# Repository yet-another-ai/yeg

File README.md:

# yeg
Yet Another Open-source EEG Device

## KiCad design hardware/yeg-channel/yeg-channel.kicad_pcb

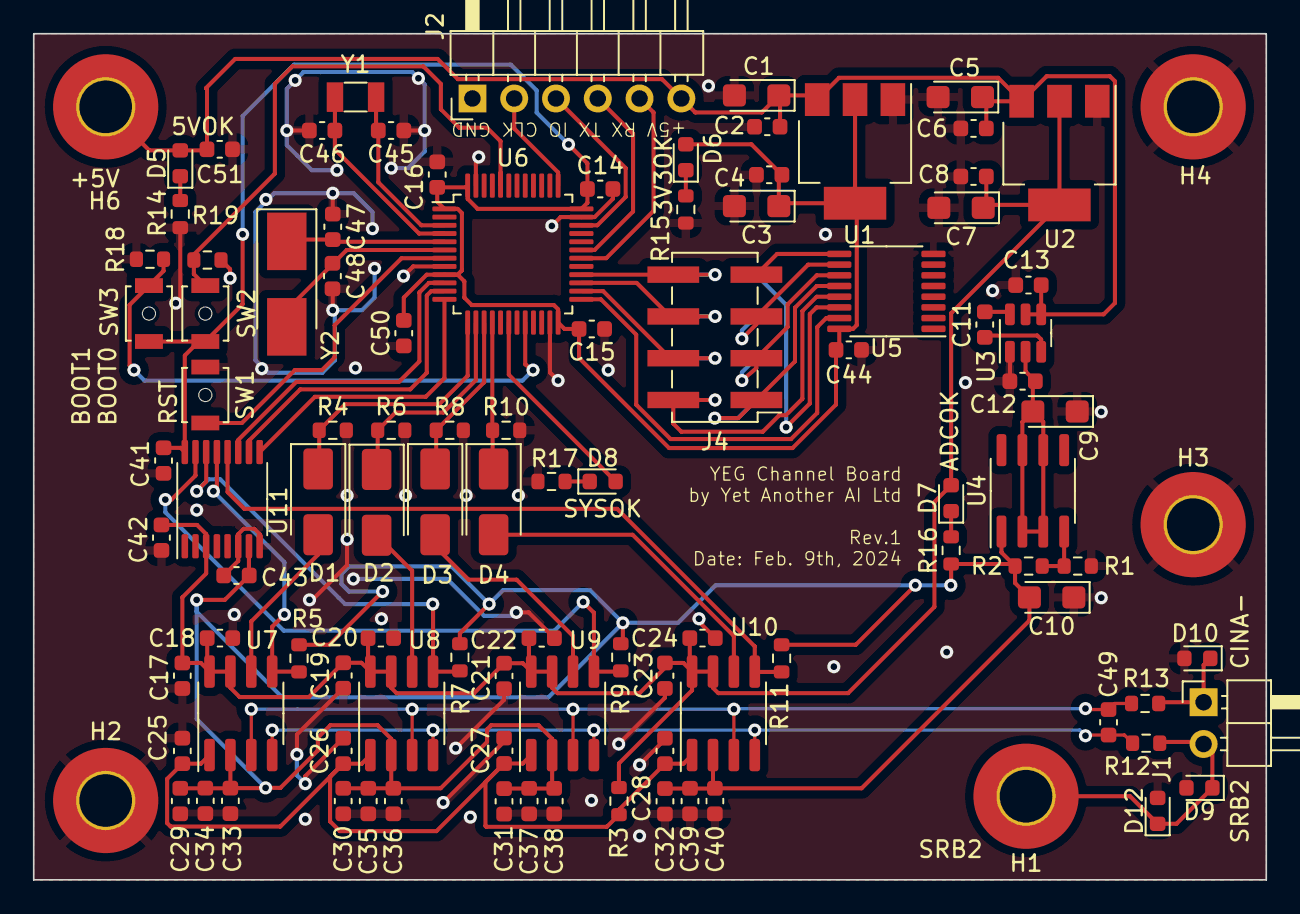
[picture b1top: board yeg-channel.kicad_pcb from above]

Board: 2 copper layers, 74.9 x 51.4 mm, 106 parts (1 on the bottom side), 55 nets.

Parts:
C1, C3, C5, C7: 22u; CP_EIA-3216-10_Kemet-I
C2, C4, C6, C8, C13, C14, C15, C16, C17, C18, C19, C20, C21, C22, C23, C24, C25, C26, C27, C28, C29, C30, C31, C32, C33, C34, C35, C36, C37, C38, C39, C40, C41, C42, C43, C44, C49, C50, C51: 100n; C_0603_1608Metric
C9, C10: 1u; CP_EIA-3216-10_Kemet-I
C11, C12: 3.3u; C_0603_1608Metric
C45, C46: 12p; C_0603_1608Metric
C47, C48: 20p; C_0603_1608Metric
D1, D2, D3, D4: SS14; D_SMA
D5: LED_5VOK; LED_0603_1608Metric
D6: LED_3V3OK; LED_0603_1608Metric
D7: LED_ADCOK; LED_0603_1608Metric
D8: LED_SYSOK; LED_0603_1608Metric
D9, D10, D12: D_TVS; D_0603_1608Metric
H1: SRB2; MountingHole_3.2mm_M3_Pad_TopBottom
H2, H3, H4: GND; MountingHole_3.2mm_M3_Pad_TopBottom
H6: 5V; MountingHole_3.2mm_M3_Pad_TopBottom
J1: Conn_ADC; PinHeader_1x02_P2.54mm_Horizontal
J2: Conn_Debug; PinHeader_1x06_P2.54mm_Horizontal
J3: Conn_SPI_Input; PinSocket_2x04_P2.54mm_Vertical_SMD
J4: Conn_SPI_Output; PinHeader_2x04_P2.54mm_Vertical_SMD
R1, R2: 240; R_0603_1608Metric
R3: 10; R_0603_1608Metric
R4, R6, R8, R10: 40k; R_0603_1608Metric
R5, R7, R9, R11, R18, R19: 10k; R_0603_1608Metric
R12, R13: 200; R_0603_1608Metric
R14, R16: 100; R_0603_1608Metric
R15, R17: 24; R_0603_1608Metric
SW1: SW_RST; SW_SPST_B3U-1000P-B
SW2: SW_BOOT0; SW_SPST_B3U-1000P-B
SW3: SW_BOOT1; SW_SPST_B3U-1000P-B
U1: AMS1117-3.3; SOT-223-3_TabPin2
U2: AMS1117-2.5; SOT-223-3_TabPin2
U3: LM2664M6X; SOT-23-6
U4: LM337L_SO8; SOIC-8_3.9x4.9mm_P1.27mm
U5: 74HC595; TSSOP-16_4.4x5mm_P0.65mm
U6: CH32V103C8T6; LQFP-48_7x7mm_P0.5mm
U7, U8, U9, U10: HX71708; SOP-8_3.76x4.96mm_P1.27mm
U11: 74HC4051; TSSOP-16_4.4x5mm_P0.65mm
Y1: 32.768k; Crystal_SMD_3215-2Pin_3.2x1.5mm
Y2: 8M; Crystal_SMD_5032-2Pin_5.0x3.2mm_HandSoldering

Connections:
+2V5: C7.1, C8.1, C17.1, C18.1, C19.1, C20.1, C21.1, C22.1, C23.1, C24.1, C42.1, D7.2 (A), R3.1, U2.2 (VO), U7.7 (DVDD), U7.8 (AVDD), U8.7 (DVDD), U8.8 (AVDD), U9.7 (DVDD), U9.8 (AVDD), U10.7 (DVDD), U10.8 (AVDD), U11.3 (A)
+3V3: C3.1, C4.1, C14.1, C15.1, C16.1, C41.1, C44.1, C50.1, D6.2 (A), SW2.2, SW3.2, U1.2 (VO), U5.16 (VCC), U6.1 (VBAT), U6.9 (VDDA), U6.24 (VDD), U6.36 (VDD), U6.48 (VDD), U11.16 (VCC)
+5V: C1.1, C2.1, C5.1, C6.1, C13.1, C51.1, D5.2 (A), H6.1, J2.6, U1.3 (VI), U2.3 (VI), U3.4 (SD), U3.5 (V+)
-2V5: C10.2, C29.2, C30.2, C31.2, C32.2, C33.2, C34.2, C35.2, C36.2, C37.2, C38.2, C39.2, C40.2, C43.2, R2.2, R5.2, R7.2, R9.2, R11.2, R16.2, U4.1 (VO), U7.2 (GND), U8.2 (GND), U9.2 (GND), U10.2 (GND), U11.7 (VEE)
-5V: C9.2, C12.1, U3.2 (OUT), U4.2 (VI), U4.3 (VI), U4.6 (VI), U4.7 (VI)
/ADC/CINA-: D10.1 (A1), J1.1, R13.1
/ADC/CS0: U6.10 (PA0), U11.11 (S0)
/ADC/CS1: U6.11 (PA1), U11.10 (S1)
/ADC/CS2: U6.12 (PA2), U11.9 (S2)
/ADC/DOUT0: D1.1 (K), R4.1, U6.13 (PA3)
/ADC/DOUT1: D2.1 (K), R6.1, U6.14 (PA4)
/ADC/DOUT2: D3.1 (K), R8.1, U6.15 (PA5)
/ADC/DOUT3: D4.1 (K), R10.1, U6.16 (PA6)
/ADC/IN+: C49.1, R12.2, U7.4 (IN+), U8.4 (IN+), U9.4 (IN+), U10.4 (IN+)
/ADC/IN-: C49.2, R13.2, U7.3 (IN-), U8.3 (IN-), U9.3 (IN-), U10.3 (IN-)
/ADC/PD_SCK0: R5.1, U7.5 (PD_SCK), U11.13 (A0)
/ADC/PD_SCK1: R7.1, U8.5 (PD_SCK), U11.14 (A1)
/ADC/PD_SCK2: R9.1, U9.5 (PD_SCK), U11.15 (A2)
/ADC/PD_SCK3: R11.1, U10.5 (PD_SCK), U11.12 (A3)
/ADC/SRB2: D9.1 (A1), D12.1 (A1), H1.1, J1.2, R12.1
/Connector/BOOT0: R19.1, SW2.1, U6.44 (BOOT0)
/Connector/BOOT1: R18.1, SW3.1, U6.20 (PB2)
/Connector/CS_IN: J3.7, U5.14 (SER)
/Connector/CS_OUT: J4.7, U5.9 (QH')
/Connector/NRST: SW1.1, U6.7 (NRST)
/Connector/RCLK: J3.1, J4.1, U5.12 (RCLK)
/Connector/SPI_MISO: J3.6, J4.6, U6.27 (PB14)
/Connector/SPI_MOSI: J3.8, J4.8, U6.28 (PB15)
/Connector/SPI_SCK: J3.4, J4.4, U6.26 (PB13)
/Connector/SRCLK: J3.3, J4.3, U5.11 (SRCLK)
/Connector/SWDCLK: J2.2, U6.37 (PA14)
/Connector/SWDIO: J2.3, U6.34 (PA13)
/Connector/SYSOK: D8.2 (A), U6.18 (PB0)
/Connector/UART1_RX: J2.4, U6.31 (PA10)
/Connector/UART1_TX: J2.5, U6.30 (PA9)
/Connector/~OE: J3.2, J4.2, U5.13 (~OE)
/Connector/~SRCLR: J3.5, J4.5, U5.10 (~SRCLR)
/MCU/OSC32_IN: C45.2, U6.3 (PC14), Y1.1
/MCU/OSC32_OUT: C46.1, U6.4 (PC15), Y1.2
/MCU/OSC_IN: C47.2, U6.5 (PD0), Y2.1
/MCU/OSC_OUT: C48.1, U6.6 (PD1), Y2.2
/MCU/SPI_CS: U5.15 (QA), U6.25 (PB12)
GND: C1.2, C2.2, C3.2, C4.2, C5.2, C6.2, C7.2, C8.2, C9.1, C10.1, C12.2, C13.2, C14.2, C15.2, C16.2, C17.2, C18.2, C19.2, C20.2, C21.2, C22.2, C23.2, C24.2, C25.2, C26.2, C27.2, C28.2, C29.1, C30.1, C31.1, C32.1, C33.1, C34.1, C35.1, C36.1, C37.1, C38.1, C39.1, C40.1, C41.2, C42.2, C43.1, C44.2, C45.1, C46.2, C47.1, C48.2, C50.2, C51.2, D9.2 (A2), D10.2 (A2), D12.2 (A2), H2.1, H3.1, H4.1, J2.1, R1.1, R4.2, R6.2, R8.2, R10.2, R14.2, R15.2, R17.2, R18.2, R19.2, SW1.2, U1.1 (GND), U2.1 (GND), U3.1 (GND), U5.8 (GND), U6.8 (VSSA), U6.23 (VSS), U6.35 (VSS), U6.47 (VSS), U11.6 (~E), U11.8 (GND)
unnamed: D1.2 (A), U7.6 (DOUT)
unnamed: D2.2 (A), U8.6 (DOUT)
unnamed: D3.2 (A), U9.6 (DOUT)
unnamed: D4.2 (A), U10.6 (DOUT)
unnamed: D5.1 (K), R14.1
unnamed: D6.1 (K), R15.1
unnamed: D7.1 (K), R16.1
unnamed: D8.1 (K), R17.1
unnamed: C11.1, U3.6 (CAP+)
unnamed: C11.2, U3.3 (CAP-)
unnamed: R1.2, R2.1, U4.4 (ADJ)
VDDA: C25.1, C26.1, C27.1, C28.1, R3.2, U7.1 (VREF), U8.1 (VREF), U9.1 (VREF), U10.1 (VREF)

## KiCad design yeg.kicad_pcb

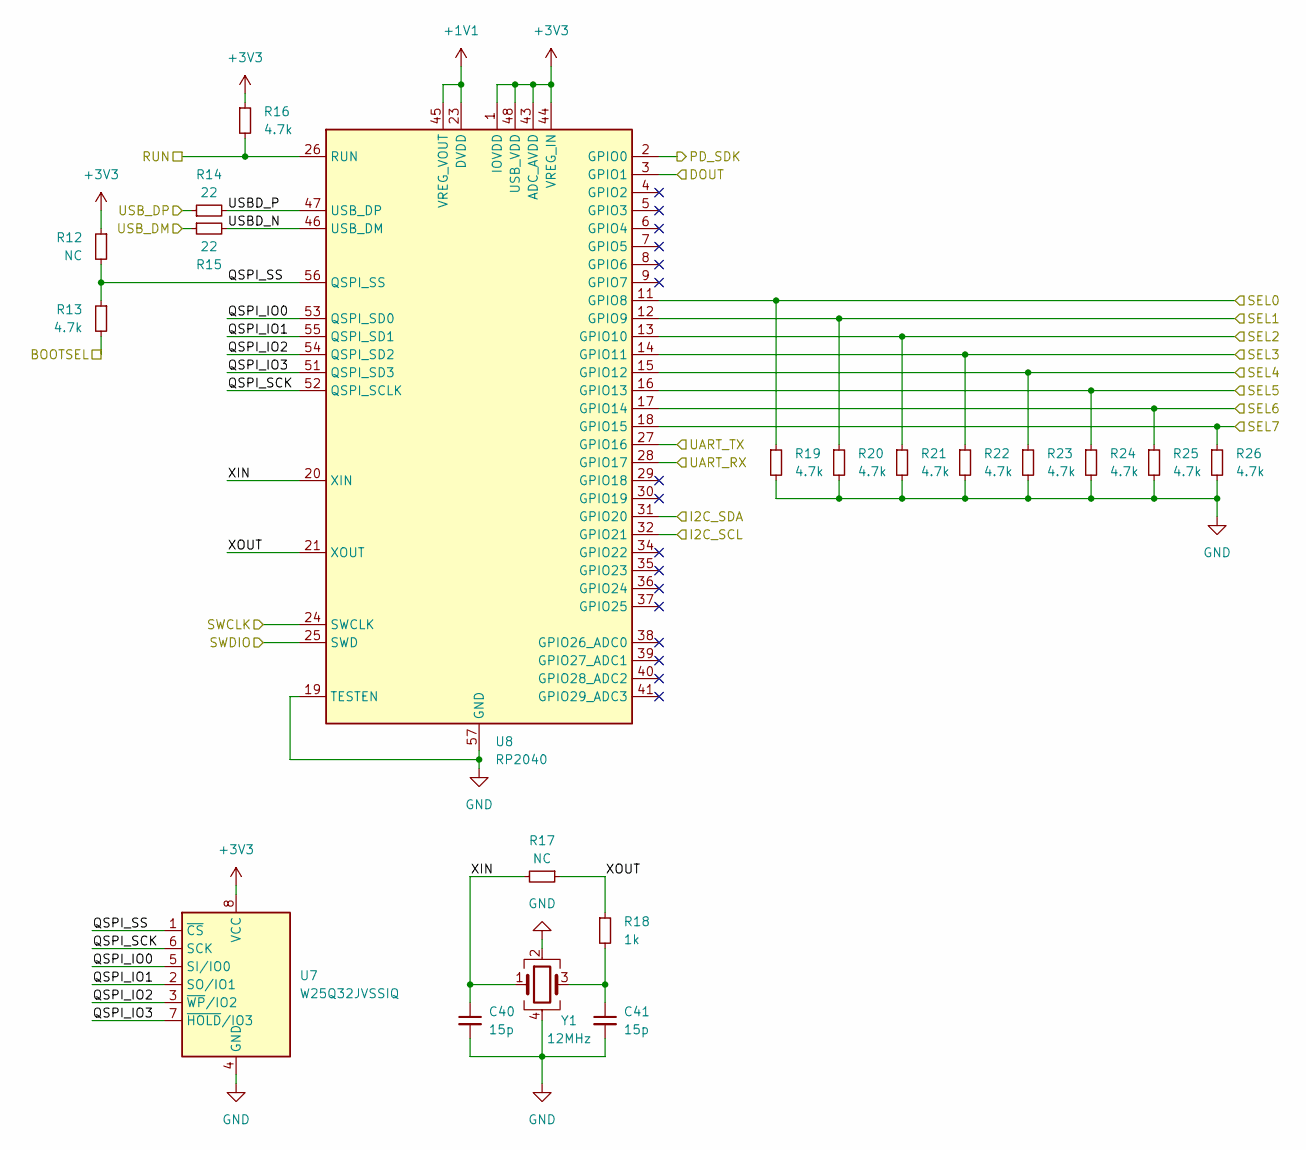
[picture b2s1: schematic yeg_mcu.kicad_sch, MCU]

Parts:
C40, C41: 15p; C_0603_1608Metric; LCSC Number C107037
R12, R17: NC; R_0603_1608Metric
R13, R16, R19, R20, R21, R22, R23, R24, R25, R26: 4.7k; R_0603_1608Metric; LCSC Number C23162
R14, R15: 22; R_0603_1608Metric; LCSC Number C23345
R18: 1k; R_0603_1608Metric; LCSC Number C21190
U7: W25Q32JVSSIQ; SOIC-8_5.275x5.275mm_P1.27mm; LCSC Number C179173
U8: RP2040; QFN-56-1EP_7x7mm_P0.4mm_EP3.2x3.2mm; LCSC Number C2040
Y1: 12MHz; Crystal_SMD_3225-4Pin_3.2x2.5mm; LCSC Number C9002

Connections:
+1V1: U8.23 (DVDD), U8.45 (VREG_VOUT), U8.50 (DVDD); also elsewhere on the board
+3V3: R12.1, R16.1, U7.8 (VCC), U8.1 (IOVDD), U8.10 (IOVDD), U8.22 (IOVDD), U8.33 (IOVDD), U8.42 (IOVDD), U8.43 (ADC_AVDD), U8.44 (VREG_IN), U8.48 (USB_VDD), U8.49 (IOVDD); also elsewhere on the board
/ADC/DOUT: U8.3 (GPIO1); also elsewhere on the board
/ADC/PD_SCK: U8.2 (GPIO0); also elsewhere on the board
/Connectors/BOOTSEL: R13.2; also elsewhere on the board
/Connectors/I2C_SCL: U8.32 (GPIO21); also elsewhere on the board
/Connectors/I2C_SDA: U8.31 (GPIO20); also elsewhere on the board
/Connectors/RUN: R16.2, U8.26 (RUN); also elsewhere on the board
/Connectors/SEL0: R19.1, U8.11 (GPIO8); also elsewhere on the board
/Connectors/SEL1: R20.1, U8.12 (GPIO9); also elsewhere on the board
/Connectors/SEL2: R21.1, U8.13 (GPIO10); also elsewhere on the board
/Connectors/SEL3: R22.1, U8.14 (GPIO11); also elsewhere on the board
/Connectors/SEL4: R23.1, U8.15 (GPIO12); also elsewhere on the board
/Connectors/SEL5: R24.1, U8.16 (GPIO13); also elsewhere on the board
/Connectors/SEL6: R25.1, U8.17 (GPIO14); also elsewhere on the board
/Connectors/SEL7: R26.1, U8.18 (GPIO15); also elsewhere on the board
/Connectors/SWCLK: U8.24 (SWCLK); also elsewhere on the board
/Connectors/SWDIO: U8.25 (SWD); also elsewhere on the board
/Connectors/UART_RX: U8.28 (GPIO17); also elsewhere on the board
/Connectors/UART_TX: U8.27 (GPIO16); also elsewhere on the board
/Connectors/USBDM: R15.1; also elsewhere on the board
/Connectors/USBDP: R14.1; also elsewhere on the board
/MCU/QSPI_IO0: U7.5 (SI/IO0), U8.53 (QSPI_SD0)
/MCU/QSPI_IO1: U7.2 (SO/IO1), U8.55 (QSPI_SD1)
/MCU/QSPI_IO2: U7.3 (~WP/IO2), U8.54 (QSPI_SD2)
/MCU/QSPI_IO3: U7.7 (~HOLD/IO3), U8.51 (QSPI_SD3)
/MCU/QSPI_SCK: U7.6 (SCK), U8.52 (QSPI_SCLK)
/MCU/QSPI_SS: R12.2, R13.1, U7.1 (~CS), U8.56 (QSPI_SS)
/MCU/USBD_N: R15.2, U8.46 (USB_DM)
/MCU/USBD_P: R14.2, U8.47 (USB_DP)
/MCU/XIN: C40.1, R17.2, U8.20 (XIN), Y1.1
/MCU/XOUT: R17.1, R18.1, U8.21 (XOUT)
GND: C40.2, C41.2, R19.2, R20.2, R21.2, R22.2, R23.2, R24.2, R25.2, R26.2, U7.4 (GND), U8.19 (TESTEN), U8.57 (GND), Y1.2, Y1.4; also elsewhere on the board
unnamed: C41.1, R18.2, Y1.3

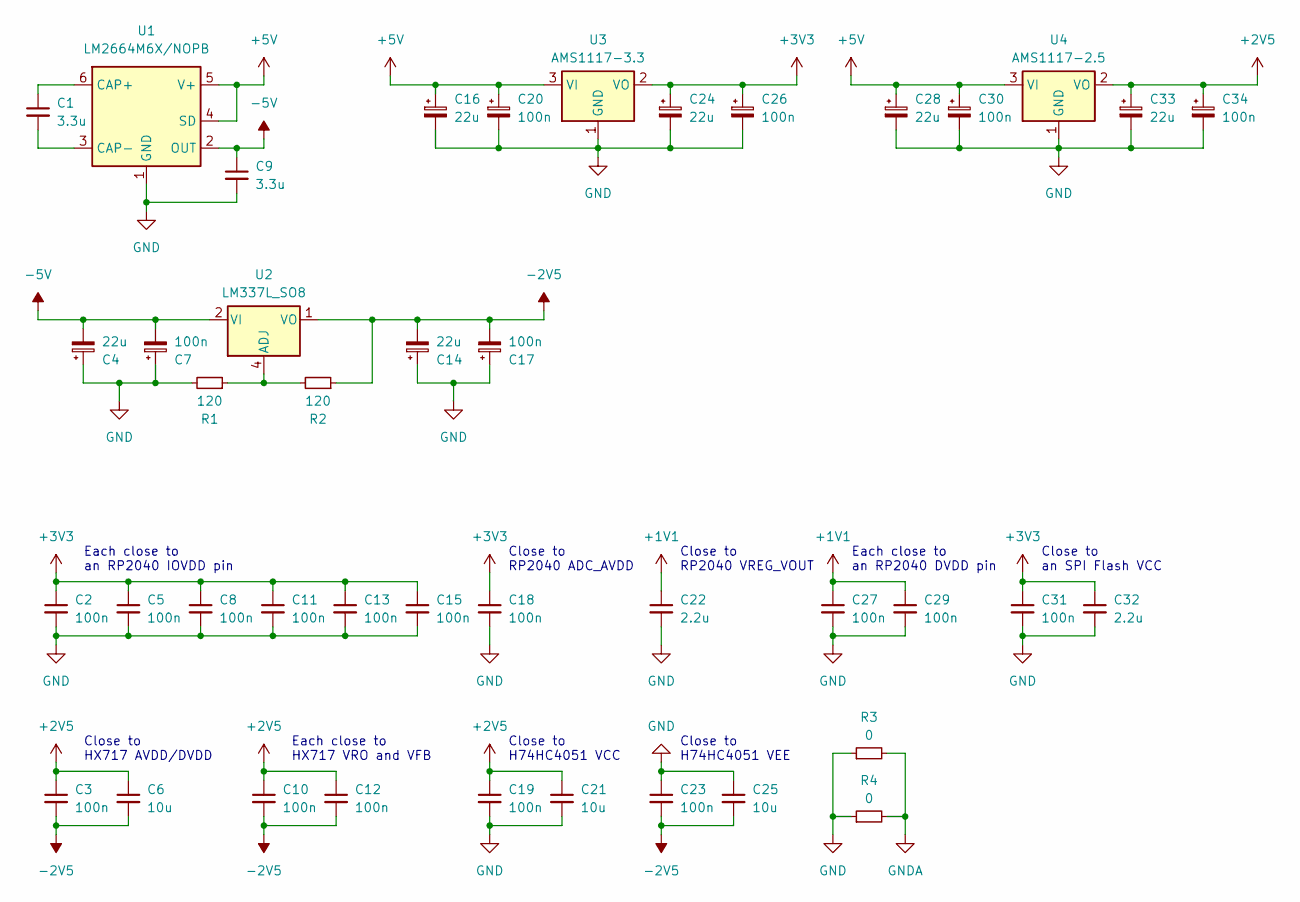
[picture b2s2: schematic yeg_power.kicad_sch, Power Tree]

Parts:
C1, C9: 3.3u; C_0603_1608Metric; LCSC Number C51412
C2, C3, C5, C8, C10, C11, C12, C13, C15, C18, C19, C23, C27, C29, C31: 100n; C_0603_1608Metric; LCSC Number C14663
C4, C14, C16, C24, C28, C33: 22u; C_1206_3216Metric; LCSC Number C1953590
C6, C21, C25: 10u; C_0603_1608Metric; LCSC Number C19702
C7, C17, C20, C26, C30, C34: 100n; C_1206_3216Metric; LCSC Number C1952859
C22, C32: 2.2u; C_0603_1608Metric; LCSC Number C23630
R1, R2: 120; R_0603_1608Metric; LCSC Number C22787
R3, R4: 0; R_0603_1608Metric; LCSC Number C21189
U1: LM2664M6X/NOPB; SOT-23-6; LCSC Number C108573
U2: LM337L_SO8; SOIC-8_3.9x4.9mm_P1.27mm; LCSC Number C544819
U3: AMS1117-3.3; SOT-223-3_TabPin2; LCSC Number C347222
U4: AMS1117-2.5; SOT-223-3_TabPin2; LCSC Number C347221

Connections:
+1V1: C22.1, C27.1, C29.1; also elsewhere on the board
+2V5: C3.1, C6.1, C10.1, C12.1, C19.1, C21.1, C33.1, C34.1, U4.2 (VO); also elsewhere on the board
+3V3: C2.1, C5.1, C8.1, C11.1, C13.1, C15.1, C18.1, C24.1, C26.1, C31.1, C32.1, U3.2 (VO); also elsewhere on the board
+5V: C16.1, C20.1, C28.1, C30.1, U1.4 (SD), U1.5 (V+), U3.3 (VI), U4.3 (VI); also elsewhere on the board
-2V5: C3.2, C6.2, C10.2, C12.2, C14.2, C17.2, C23.2, C25.2, R2.1, U2.1 (VO); also elsewhere on the board
-5V: C4.2, C7.2, C9.1, U1.2 (OUT), U2.2 (VI), U2.3 (VI), U2.6 (VI), U2.7 (VI)
GND: C2.2, C4.1, C5.2, C7.1, C8.2, C9.2, C11.2, C13.2, C14.1, C15.2, C16.2, C17.1, C18.2, C19.2, C20.2, C21.2, C22.2, C23.1, C24.2, C25.1, C26.2, C27.2, C28.2, C29.2, C30.2, C31.2, C32.2, C33.2, C34.2, R1.2, R3.1, R4.1, U1.1 (GND), U3.1 (GND), U4.1 (GND); also elsewhere on the board
GNDA: R3.2, R4.2; also elsewhere on the board
unnamed: C1.1, U1.6 (CAP+)
unnamed: C1.2, U1.3 (CAP-)
unnamed: R1.1, R2.2, U2.4 (ADJ)

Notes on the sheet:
Close to H74HC4051 VEE
Close to RP2040 VREG_VOUT
Each close to an RP2040 IOVDD pin
Close to RP2040 ADC_AVDD
Each close to HX717 VRO and VFB
Each close to an RP2040 DVDD pin
Close to an SPI Flash VCC
Close to HX717 AVDD/DVDD
Close to H74HC4051 VCC

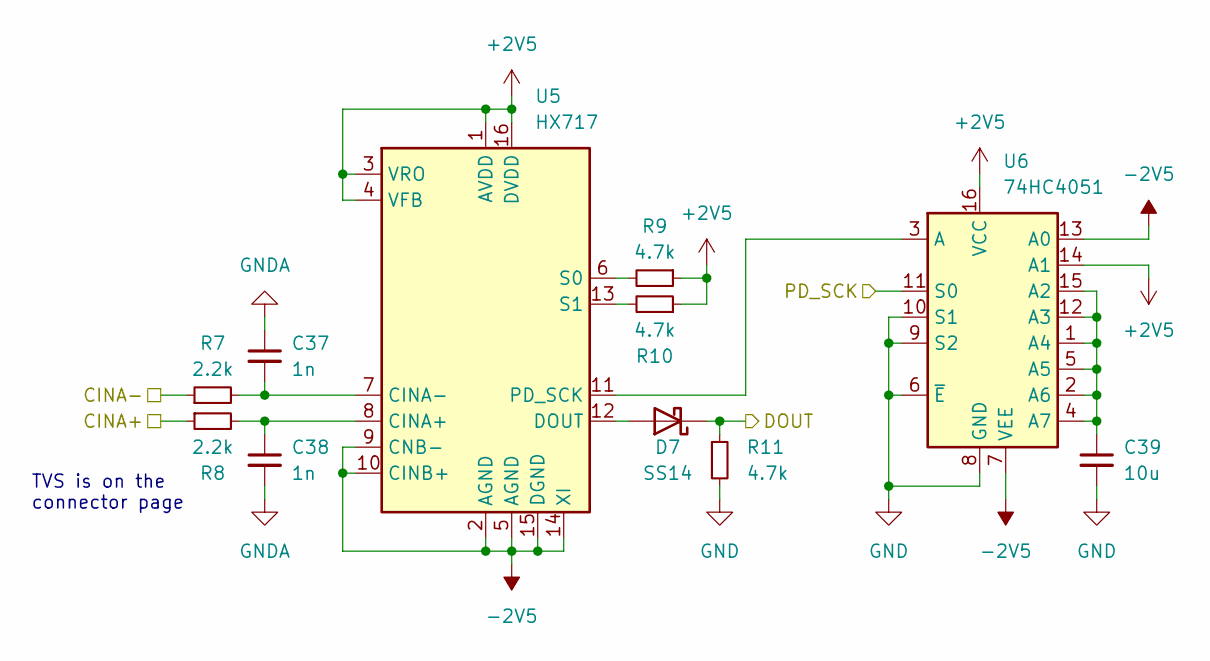
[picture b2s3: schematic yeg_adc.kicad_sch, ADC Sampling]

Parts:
C37, C38: 1n; C_0603_1608Metric; LCSC Number C100040
C39: 10u; C_0603_1608Metric; LCSC Number C19702
D7: SS14; D_SMA; LCSC Number C83852
R7, R8: 2.2k; R_0603_1608Metric; LCSC Number C4190
R9, R10, R11: 4.7k; R_0603_1608Metric; LCSC Number C23162
U5: HX717; SOP-16_4.55x10.3mm_P1.27mm; LCSC Number C2961106
U6: 74HC4051; SOP-16_3.9x9.9mm_P1.27mm; LCSC Number C507180

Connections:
+2V5: R9.1, R10.1, U5.1 (AVDD), U5.3 (VRO), U5.4 (VFB), U5.16 (DVDD), U6.14 (A1), U6.16 (VCC); also elsewhere on the board
-2V5: U5.2 (AGND), U5.5 (AGND), U5.9 (CNB-), U5.10 (CINB+), U5.14 (XI), U5.15 (DGND), U6.7 (VEE), U6.13 (A0); also elsewhere on the board
/ADC/CINA+: R8.1; also elsewhere on the board
/ADC/CINA-: R7.1; also elsewhere on the board
/ADC/DOUT: D7.1 (K), R11.1; also elsewhere on the board
/ADC/PD_SCK: U6.11 (S0); also elsewhere on the board
GND: C39.2, R11.2, U6.6 (~E), U6.8 (GND), U6.9 (S2), U6.10 (S1); also elsewhere on the board
GNDA: C37.1, C38.2; also elsewhere on the board
unnamed: D7.2 (A), U5.12 (DOUT)
unnamed: C38.1, R8.2, U5.8 (CINA+)
unnamed: C37.2, R7.2, U5.7 (CINA-)
unnamed: U5.11 (PD_SCK), U6.3 (A)
unnamed: R9.2, U5.6 (S0)
unnamed: R10.2, U5.13 (S1)
unnamed: C39.1, U6.1 (A4), U6.2 (A6), U6.4 (A7), U6.5 (A5), U6.12 (A3), U6.15 (A2)

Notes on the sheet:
TVS is on the connector page

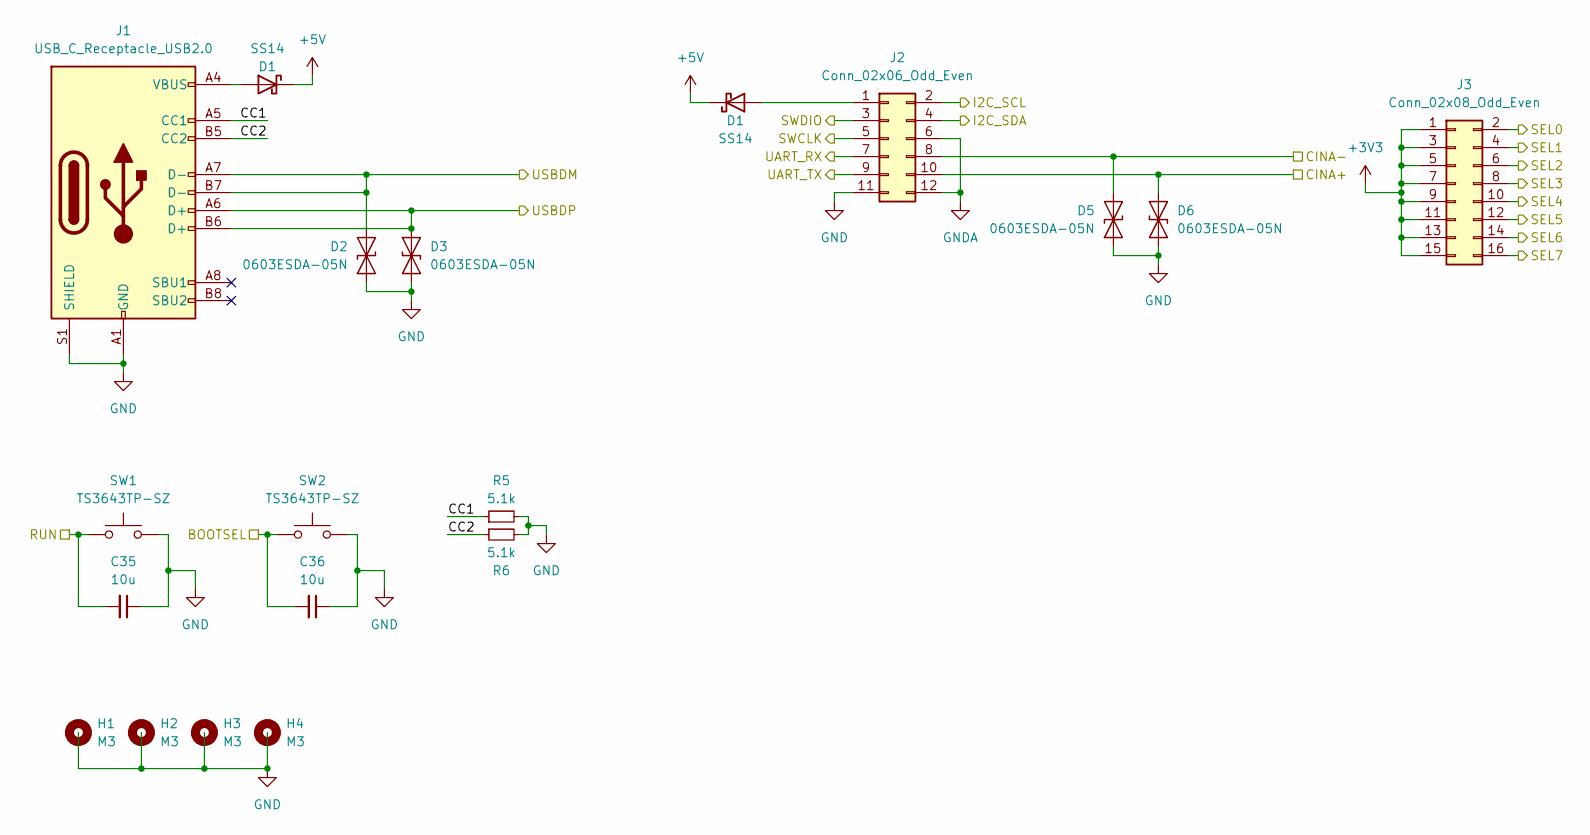
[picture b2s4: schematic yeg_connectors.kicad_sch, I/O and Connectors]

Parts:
C35, C36: 10u; C_0603_1608Metric; LCSC Number C19702
D1: SS14; D_SMA; LCSC Number C83852
D2, D3, D5, D6: 0603ESDA-05N; D_0603_1608Metric; LCSC Number C316054
H1, H2, H3, H4: M3; MountingHole_3.2mm_M3_DIN965_Pad
J1: USB_C_Receptacle_USB2.0; USB_C_Receptacle_XKB_U262-16XN-4BVC11; LCSC Number C319148
J2: Conn_02x06_Odd_Even; PinHeader_2x06_P2.54mm_Vertical; LCSC Number C492423
J3: Conn_02x08_Odd_Even; PinHeader_2x08_P2.54mm_Vertical; LCSC Number C68234
R5, R6: 5.1k; R_0603_1608Metric; LCSC Number C23186
SW1, SW2: TS3643TP-SZ; SW_SPST_EVQPE1; LCSC Number C2681479

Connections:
+3V3: J3.1, J3.3, J3.5, J3.7, J3.9, J3.11, J3.13, J3.15; also elsewhere on the board
+5V: D1.1 (K); also elsewhere on the board
/ADC/CINA+: D6.1 (A1), J2.10; also elsewhere on the board
/ADC/CINA-: D5.1 (A1), J2.8; also elsewhere on the board
/Connectors/BOOTSEL: C36.2, SW2.1; also elsewhere on the board
/Connectors/CC1: J1.A5 (CC1), R5.1
/Connectors/CC2: J1.B5 (CC2), R6.1
/Connectors/I2C_SCL: J2.2; also elsewhere on the board
/Connectors/I2C_SDA: J2.4; also elsewhere on the board
/Connectors/RUN: C35.2, SW1.1; also elsewhere on the board
/Connectors/SEL0: J3.2; also elsewhere on the board
/Connectors/SEL1: J3.4; also elsewhere on the board
/Connectors/SEL2: J3.6; also elsewhere on the board
/Connectors/SEL3: J3.8; also elsewhere on the board
/Connectors/SEL4: J3.10; also elsewhere on the board
/Connectors/SEL5: J3.12; also elsewhere on the board
/Connectors/SEL6: J3.14; also elsewhere on the board
/Connectors/SEL7: J3.16; also elsewhere on the board
/Connectors/SWCLK: J2.5; also elsewhere on the board
/Connectors/SWDIO: J2.3; also elsewhere on the board
/Connectors/UART_RX: J2.7; also elsewhere on the board
/Connectors/UART_TX: J2.9; also elsewhere on the board
/Connectors/USBDM: D2.1 (A1), J1.A7 (D-), J1.B7 (D-); also elsewhere on the board
/Connectors/USBDP: D3.1 (A1), J1.A6 (D+), J1.B6 (D+); also elsewhere on the board
GND: C35.1, C36.1, D2.2 (A2), D3.2 (A2), D5.2 (A2), D6.2 (A2), J1.A1 (GND), J1.A12 (GND), J1.B1 (GND), J1.B12 (GND), J1.S1 (SHIELD), J2.11, R5.2, R6.2, SW1.2, SW2.2; also elsewhere on the board
GNDA: J2.6, J2.12; also elsewhere on the board

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
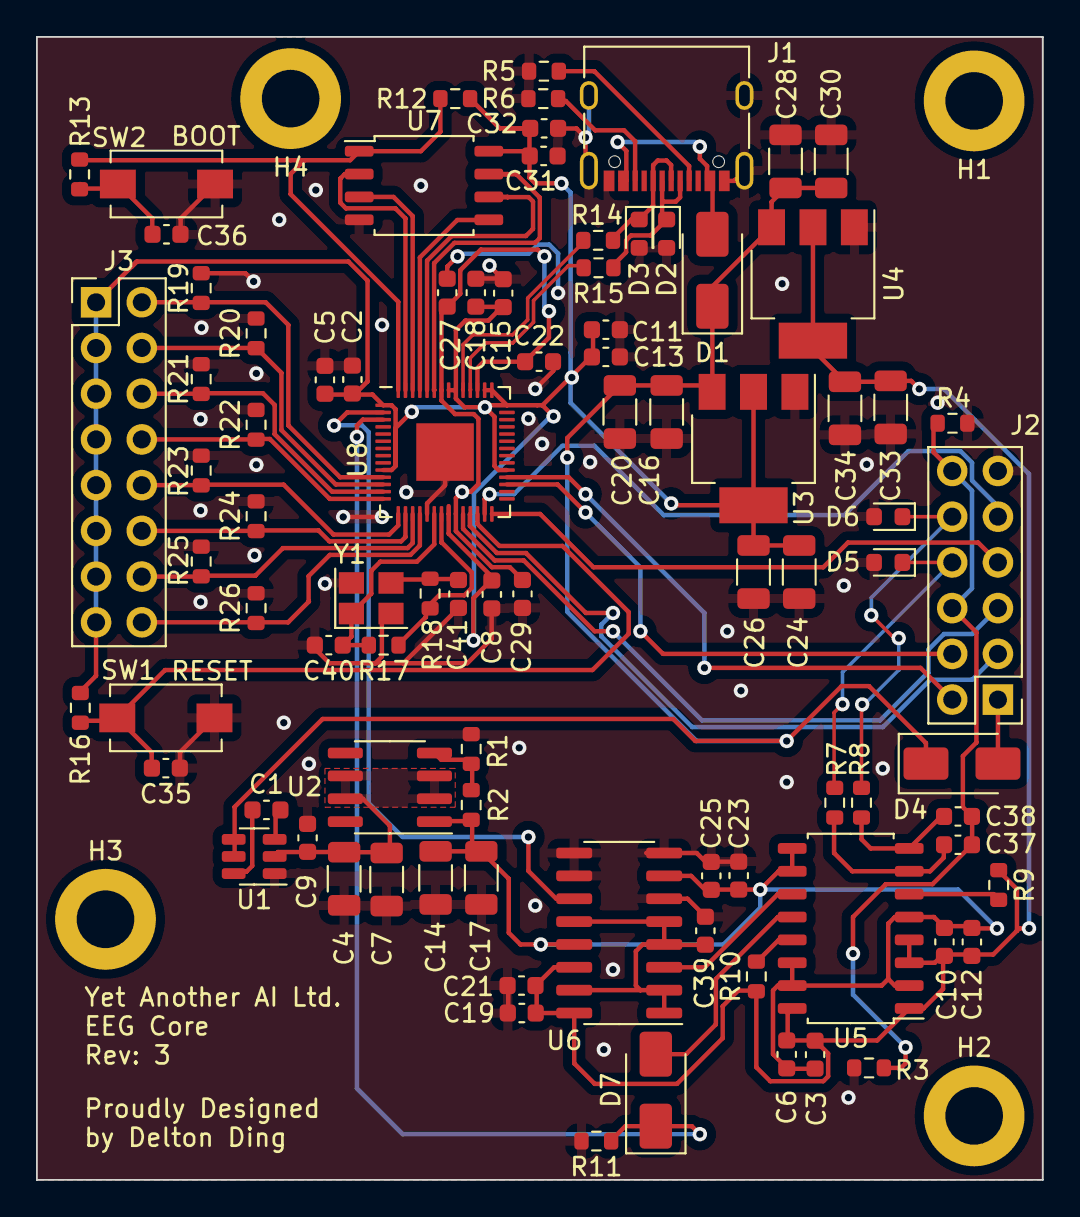
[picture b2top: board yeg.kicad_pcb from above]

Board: 2 copper layers, 55.9 x 63.5 mm, 92 parts (0 on the bottom side), 55 nets.

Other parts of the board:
D4: SS14; D_SMA

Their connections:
+5V: D4.1 (K); also elsewhere on the board

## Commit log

2024-02-06 init project
2024-02-07 refactor
2024-02-07 remove backup files
2024-02-08 fixes and add pcb layout
2024-02-08 fix debug port
2024-02-08 move srb2 to a closer port
2024-02-08 fix bom
2024-02-08 add gerber add pos files
